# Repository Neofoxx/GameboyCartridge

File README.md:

# Gameboy Cartridge with a PIC32

A Gameboy cartridge with a microcontroller on it, for quick tests on actual hardware 

## Overview

This projects implements a simple 32kB ROM + 8kB SRAM cartridge, where both are replaced with SRAM chips, and populated by a PIC32MM microcontroller at either boot, or via a USB interface.

Currently working:
- Uploading to the "ROM" part of the cartridge
- Resetting etc.
- Tested that Tetris is playable, if a write to 0x2000 is patched out

Future plans:
- "SRAM" part of cartridge tested
- Speedup of upload/readout scripts

Not planned:
- Bigger size of "ROM"

## Theory of operation

In a normal gameboy cartrdige without an MBC, there is usually just a ROM chip, that contains the game. An exmaple of this would be Tetris. This is memory mapped into the Gameboys address space, and can be 32kB max.

There is also space for an 8kB RAM chip - usually SRAM, which means a battery is required to save the contents. FRAM chips are available nowadays, and remove the battery requirements, at the expense of increased cost. This is also memory mapped, but needs a few logic for address decoding.

In this implementation, both ROM and RAM are replaced with 32kB SRAM chips. One is used as the ROM, the other (well, part of it) is used as SRAM.

The idea is, that for speeds testing on real HW, code can be uploaded from the PC to the Gameboy via the USB connection, removing the need to unplug the cartridge, insert it into the programmer, flash it, remove it, reinstall it, and then test. Convenience is what we're after.

The other idea is for the microcontroller to have a 40kB section of FLASH dedicated to storing said contents, and automatically populating the chips at power-up.

## TODOs

Fix board files. Forgot to connect some pins to the transistors...

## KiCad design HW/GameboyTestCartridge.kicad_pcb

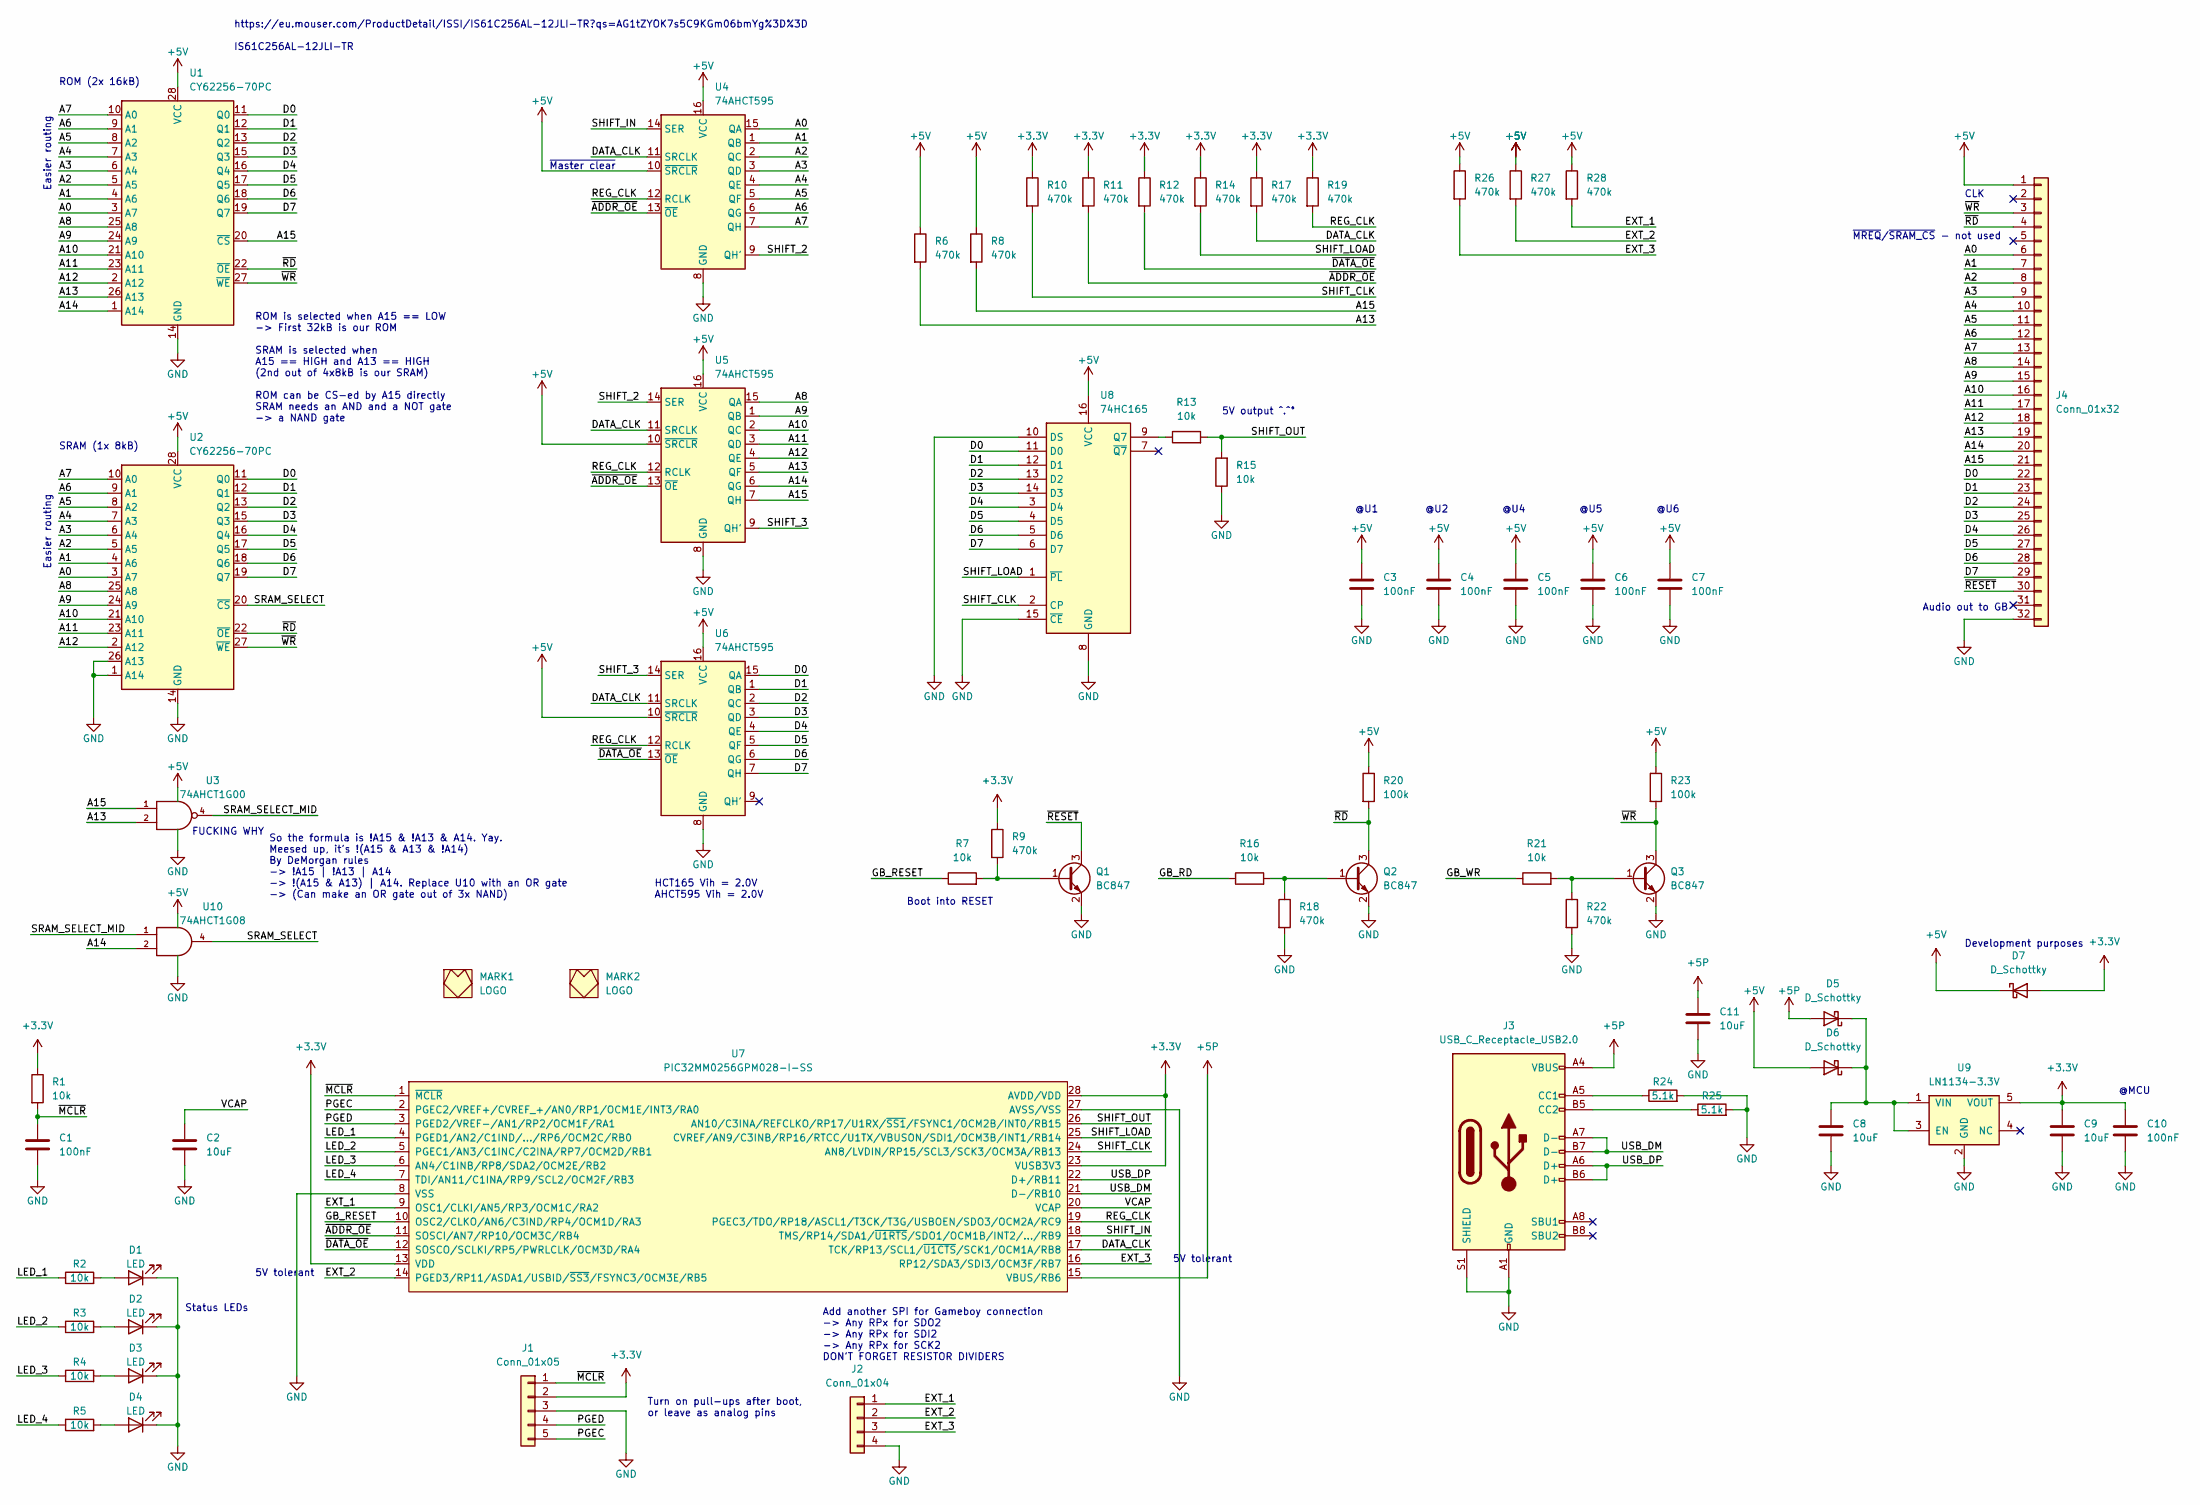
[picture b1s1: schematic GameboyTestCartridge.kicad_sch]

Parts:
C1, C3, C4, C5, C6, C7, C10: 100nF; C_0603_1608Metric
C2, C8, C9, C11: 10uF; C_0805_2012Metric
D1, D2, D3, D4: LED; LED_0603_1608Metric
D5, D6, D7: D_Schottky; D_SOD-323
J1: Conn_01x05; PinHeader_1x05_P2.54mm_Horizontal
J2: Conn_01x04; PinHeader_1x04_P2.54mm_Horizontal
J3: USB_C_Receptacle_USB2.0; Jing_USB_C_2_0_16pin_receptable_noSlots
J4: Conn_01x32; GameboyCartridge
MARK1: LOGO; FOX_LOGO_MASK
MARK2: LOGO; FOX_LOGO_SILK
Q1, Q2, Q3: BC847; SOT-23
R1, R2, R3, R4, R5, R7, R13, R15, R16, R21: 10k; R_0603_1608Metric
R6, R8, R9, R10, R11, R12, R14, R17, R18, R19, R22, R26, R27, R28: 470k; R_0603_1608Metric
R20, R23: 100k; R_0603_1608Metric
R24, R25: 5.1k; R_0603_1608Metric
U1, U2: CY62256-70PC; SOIC-28W_7.5x17.9mm_P1.27mm
U3: 74AHCT1G00; SOT-23-5
U4, U5, U6: 74AHCT595; SOIC-16_3.9x9.9mm_P1.27mm
U7: PIC32MM0256GPM028-I-SS; SSOP-28_5.3x10.2mm_P0.65mm
U8: 74HC165; SOIC-16_3.9x9.9mm_P1.27mm
U9: LN1134-3.3V; SOT-23-5
U10: 74AHCT1G08; SOT-23-5

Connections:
+3.3V: C9.1, C10.1, D7.2 (A), J1.2, R1.1, R9.1, R10.1, R11.1, R12.1, R14.1, R17.1, R19.1, U7.13 (VDD), U7.23 (VUSB3V3), U7.28 (AVDD/VDD), U9.5 (VOUT)
+5P: C11.1, D5.2 (A), J3.A4 (VBUS), J3.A9 (VBUS), J3.B4 (VBUS), J3.B9 (VBUS), U7.15 (VBUS/RB6)
+5V: C3.1, C4.1, C5.1, C6.1, C7.1, D6.2 (A), D7.1 (K), J4.1, R6.1, R8.1, R20.1, R23.1, R26.1, R27.1, R28.1, U1.28 (VCC), U2.28 (VCC), U3.5 (VCC), U4.10 (~SRCLR), U4.16 (VCC), U5.10 (~SRCLR), U5.16 (VCC), U6.10 (~SRCLR), U6.16 (VCC), U8.16 (VCC), U10.5 (VCC)
/A0: J4.6, U1.3 (A7), U2.3 (A7), U4.15 (QA)
/A1: J4.7, U1.4 (A6), U2.4 (A6), U4.1 (QB)
/A2: J4.8, U1.5 (A5), U2.5 (A5), U4.2 (QC)
/A3: J4.9, U1.6 (A4), U2.6 (A4), U4.3 (QD)
/A4: J4.10, U1.7 (A3), U2.7 (A3), U4.4 (QE)
/A5: J4.11, U1.8 (A2), U2.8 (A2), U4.5 (QF)
/A6: J4.12, U1.9 (A1), U2.9 (A1), U4.6 (QG)
/A7: J4.13, U1.10 (A0), U2.10 (A0), U4.7 (QH)
/A8: J4.14, U1.25 (A8), U2.25 (A8), U5.15 (QA)
/A9: J4.15, U1.24 (A9), U2.24 (A9), U5.1 (QB)
/A10: J4.16, U1.21 (A10), U2.21 (A10), U5.2 (QC)
/A11: J4.17, U1.23 (A11), U2.23 (A11), U5.3 (QD)
/A12: J4.18, U1.2 (A12), U2.2 (A12), U5.4 (QE)
/A13: J4.19, R6.2, U1.26 (A13), U3.2, U5.5 (QF)
/A14: J4.20, U1.1 (A14), U5.6 (QG), U10.2
/A15: J4.21, R8.2, U1.20 (~CS), U3.1, U5.7 (QH)
/D0: J4.22, U1.11 (Q0), U2.11 (Q0), U6.15 (QA), U8.11 (D0)
/D1: J4.23, U1.12 (Q1), U2.12 (Q1), U6.1 (QB), U8.12 (D1)
/D2: J4.24, U1.13 (Q2), U2.13 (Q2), U6.2 (QC), U8.13 (D2)
/D3: J4.25, U1.15 (Q3), U2.15 (Q3), U6.3 (QD), U8.14 (D3)
/D4: J4.26, U1.16 (Q4), U2.16 (Q4), U6.4 (QE), U8.3 (D4)
/D5: J4.27, U1.17 (Q5), U2.17 (Q5), U6.5 (QF), U8.4 (D5)
/D6: J4.28, U1.18 (Q6), U2.18 (Q6), U6.6 (QG), U8.5 (D6)
/D7: J4.29, U1.19 (Q7), U2.19 (Q7), U6.7 (QH), U8.6 (D7)
/DATA_CLK: R17.2, U4.11 (SRCLK), U5.11 (SRCLK), U6.11 (SRCLK), U7.17 (TCK/RP13/SCL1/~U1CTS/SCK1/OCM1A/RB8)
/EXT_1: J2.1, R28.2, U7.9 (OSC1/CLKI/AN5/RP3/OCM1C/RA2)
/EXT_2: J2.2, R27.2, U7.14 (PGED3/RP11/ASDA1/USBID/~SS3/FSYNC3/OCM3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)
/EXT_3: J2.3, R26.2, U7.16 (RP12/SDA3/SDI3/OCM3F/RB7)
/GB_RD: R16.1
/GB_RESET: R7.1, U7.10 (OSC2/CLKO/AN6/C3IND/RP4/OCM1D/RA3)
/GB_WR: R21.1
/LED_1: R2.1, U7.4 (PGED1/AN2/C1IND/.../RP6/OCM2C/RB0)
/LED_2: R3.1, U7.5 (PGEC1/AN3/C1INC/C2INA/RP7/OCM2D/RB1)
/LED_3: R4.1, U7.6 (AN4/C1INB/RP8/SDA2/OCM2E/RB2)
/LED_4: R5.1, U7.7 (TDI/AN11/C1INA/RP9/SCL2/OCM2F/RB3)
/PGEC: J1.5, U7.2 (PGEC2/VREF+/CVREF_+/AN0/RP1/OCM1E/INT3/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)
/PGED: J1.4, U7.3 (PGED2/VREF-/AN1/RP2/OCM1F/RA1)
/REG_CLK: R19.2, U4.12 (RCLK), U5.12 (RCLK), U6.12 (RCLK), U7.19 (PGEC3/TDO/RP18/ASCL1/T3CK/T3G/USBOEN/SD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)
/SHIFT_2: U4.9 (QH'), U5.14 (SER)
/SHIFT_3: U5.9 (QH'), U6.14 (SER)
/SHIFT_CLK: R10.2, U7.24 (AN8/LVDIN/RP15/SCL3/SCK3/OCM3A/RB13), U8.2 (CP)
/SHIFT_IN: U4.14 (SER), U7.18 (TMS/RP14/SDA1/~U1RTS/SDO1/OCM1B/INT2/..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)
/SHIFT_LOAD: R14.2, U7.25 (CVREF/AN9/C3INB/RP16/RTCC/U1TX/VBUSON/S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), U8.1 (~PL)
/SHIFT_OUT: R13.2, R15.2, U7.26 (AN10/C3INA/REFCLKO/RP17/U1RX/~SS1/FSYNC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)
/SRAM_SELECT: U2.20 (~CS), U10.4
/SRAM_SELECT_MID: U3.4, U10.1
/USB_DM: J3.A7 (D-), J3.B7 (D-), U7.21 (D-/RB10)
/USB_DP: J3.A6 (D+), J3.B6 (D+), U7.22 (D+/RB11)
/VCAP: C2.1, U7.20 (VCAP)
/~ADDR_OE: R11.2, U4.13 (~OE), U5.13 (~OE), U7.11 (SOSCI/AN7/RP10/OCM3C/RB4)
/~DATA_OE: R12.2, U6.13 (~OE), U7.12 (SOSCO/SCLKI/RP5/PWRLCLK/OCM3D/RA4)
/~MCLR: C1.1, J1.1, R1.2, U7.1 (~MCLR)
/~RD: J4.4, Q2.3 (C), R20.2, U1.22 (~OE), U2.22 (~OE)
/~RESET: J4.30, Q1.3 (C)
/~WR: J4.3, Q3.3 (C), R23.2, U1.27 (~WE), U2.27 (~WE)
GND: C1.2, C2.2, C3.2, C4.2, C5.2, C6.2, C7.2, C8.2, C9.2, C10.2, C11.2, D1.1 (K), D2.1 (K), D3.1 (K), D4.1 (K), J1.3, J2.4, J3.A1 (GND), J3.A12 (GND), J3.B1 (GND), J3.B12 (GND), J3.S1 (SHIELD), J4.32, Q1.2 (E), Q2.2 (E), Q3.2 (E), R15.1, R18.2, R22.2, R24.2, R25.2, U1.14 (GND), U2.1 (A14), U2.14 (GND), U2.26 (A13), U3.3 (GND), U4.8 (GND), U5.8 (GND), U6.8 (GND), U7.8 (VSS), U7.27 (AVSS/VSS), U8.8 (GND), U8.10 (DS), U8.15 (~CE), U9.2 (GND), U10.3 (GND)
unnamed: C8.1, D5.1 (K), D6.1 (K), U9.1 (VIN), U9.3 (EN)
unnamed: D1.2 (A), R2.2
unnamed: D2.2 (A), R3.2
unnamed: D3.2 (A), R4.2
unnamed: D4.2 (A), R5.2
unnamed: J3.A5 (CC1), R24.1
unnamed: J3.B5 (CC2), R25.1
unnamed: Q1.1 (B), R7.2, R9.2
unnamed: Q2.1 (B), R16.2, R18.1
unnamed: Q3.1 (B), R21.2, R22.1
unnamed: R13.1, U8.9 (Q7)

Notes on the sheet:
ROM is selected when A15 == LOW -> First 32kB is our ROM SRAM is selected when A15 == HIGH and A13 == HIGH (2nd out of 4x8kB is our SRAM) ROM can be CS-ed by A15 directly SRAM needs an AND and a NOT gate -> a NAND gate
HCT165 Vih = 2.0V AHCT595 Vih = 2.0V
Easier routing
5V output ^.^°
Turn on pull-ups after boot, or leave as analog pins
~{Master clear}
@U5
~{MREQ}/~{SRAM_CS} - not used
@U4
FUCKING WHY
@U2
Boot into RESET
So the formula is !A15 & !A13 & A14. Yay. Meesed up, it's !(A15 & A13 & !A14) By DeMorgan rules -> !A15 | !A13 | A14 -> !(A15 & A13) | A14. Replace U10 with an OR gate -> (Can make an OR gate out of 3x NAND)
Add another SPI for Gameboy connection -> Any RPx for SDO2 -> Any RPx for SDI2 -> Any RPx for SCK2 DON'T FORGET RESISTOR DIVIDERS
Audio out to GB
5V tolerant
Development purposes
@U1
Status LEDs
ROM (2x 16kB)
SRAM (1x 8kB)
@U6
https://eu.mouser.com/ProductDetail/ISSI/IS61C256AL-12JLI-TR?qs=AG1tZYOK7s5C9KGm06bmYg%3D%3D IS61C256AL-12JLI-TR
@MCU
CLK

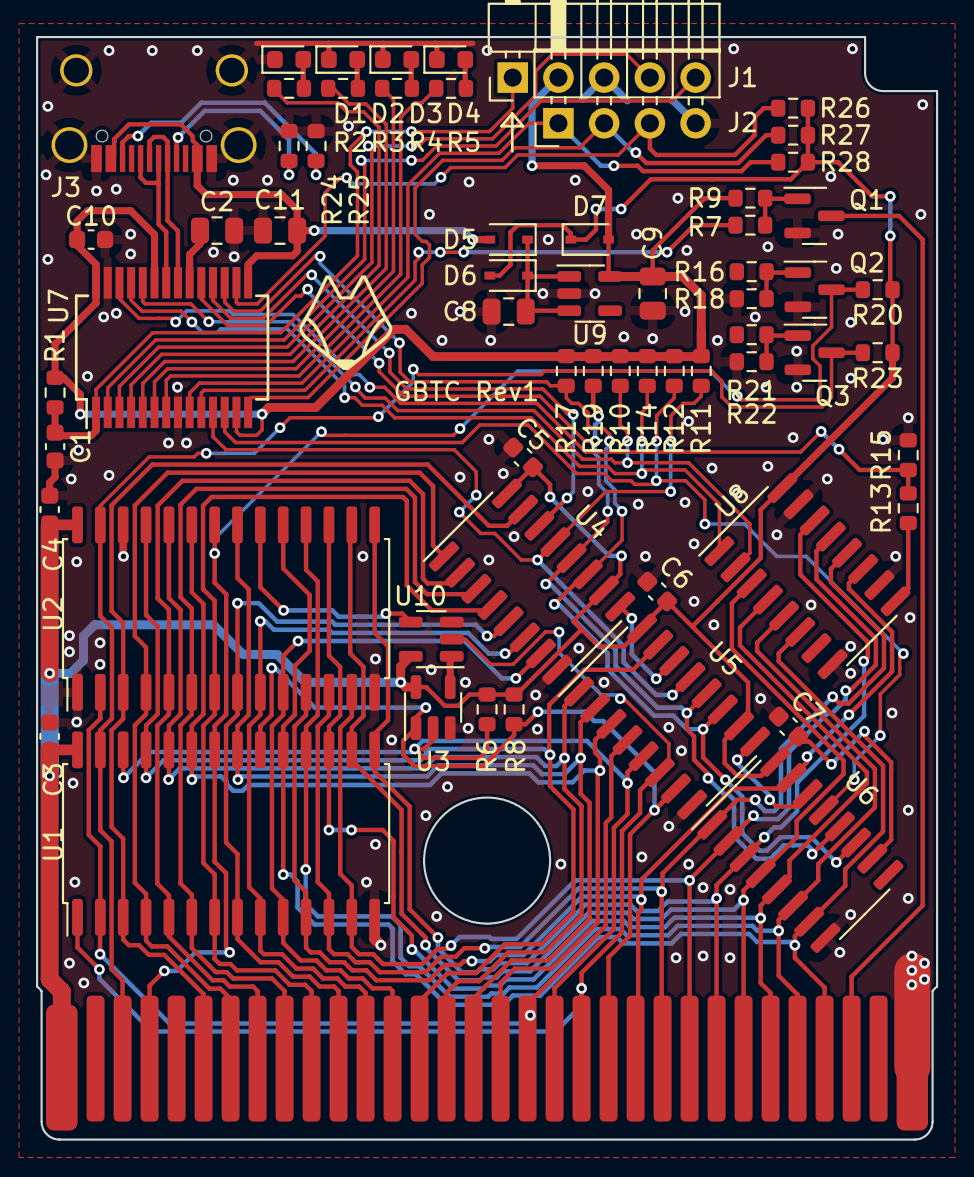
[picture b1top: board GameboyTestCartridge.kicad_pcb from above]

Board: 2 copper layers, 50.0 x 61.2 mm, 65 parts (1 on the bottom side), 68 nets.

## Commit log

2023-05-14 README add
2023-05-14 Added Rev1 HW
2023-05-14 Added FW
